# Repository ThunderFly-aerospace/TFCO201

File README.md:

# TFCO201 - ThunderFly airborne CO2 concentration sensor

The TFCO201 [carbon dioxide gas](https://en.wikipedia.org/wiki/Carbon_dioxide) sensor offers flexible integration options. It can be directly connected to a Pixhawk autopilot with PX4 firmware or used as a sensor for the [TF-ATMON monitoring system](https://www.thunderfly.cz/tf-atmon.html).

Sensors mounted on UAVs can be used for a variety of purposes. TFCO201 can measure CO2 concentrations in parallel with air temperature and humidity, which can be used for meteorological purposes. It could also be used to determine the presence of wildfires.

## Applications

In combination with the [TF-ATMON system](https://www.thunderfly.cz/tf-atmon.html), the sensor could be used in various applications. Here are a few examples. 

### Atmospheric sounding

The TFCO201 sensor could be used for [direct atmospheric sounding](https://en.wikipedia.org/wiki/Atmospheric_sounding). Here is an example of measured data taken by [TF-G2 autogyro](https://www.thunderfly.cz/tf-g2.html).

### Locating sources of atmospheric pollution (Urban Air Quality Monitoring)

A drone with a CO2 sensor can monitor carbon dioxide levels in densely populated urban areas, such UAVs can collect data on CO2 concentrations across different parts of the city, aiding authorities in identifying and addressing areas with high emissions. This data can be utilized for green space planning, improving urban transportation, and informing residents about air quality.

### Ecosystem Change Observation 
An unmanned system with a CO2 sensor can monitor changes in CO2 levels in various ecosystems, such as forests, wetlands, or agricultural lands. This information is crucial for scientists studying the impact of climate change on different types of environments and aids in predicting future ecological changes or impact mitigation methods. 

### Industrial Emission Control 
Industrial areas often contribute significantly to total CO2 emissions. A UAV with a CO2 sensor can effectively monitor and map emissions from factories, power plants, and other industrial facilities. This data can be used for emission regulation and developing strategies to reduce the carbon footprint of industrial areas.

## Where to get it?

The TFCO201 is commercially available from [ThunderFly s.r.o.](https://www.thunderfly.cz/). For a commercial quotation, contact us by email at sale@thunderfly.cz or shop at our [Tindie store](https://www.tindie.com/stores/thunderfly/).

## Parameters

| Parameter | Value | Description |
|-----------|-------|-------------|
| Sensing element | [SCD41](https://sensirion.com/media/documents/E0F04247/631EF271/CD_DS_SCD40_SCD41_Datasheet_D1.pdf) | Other possible sensors SCD40, SCD42 |
| Typical accuracy | ± (50 ppm + 5% of reading) | 400 ppm – 2’000 ppm  |
| Humidity measurement accuracy | ± 9 % RH | -10 °C – 60 °C, 0 %RH – 100 %RH  |
| Temperature measurement accuracy | ± 1.5 °C | -10 °C – 60 °C |
| Repeatability | ± 10 ppm |  |
| Operating temperature range| -10 °C – 60 °C |  |
| Operating humidity range| 0 %RH – 100 %RH | |
| I2C connector | 4-pin JST-GH | The second connector could be installed on the opposite side |
| I2C address | 0x62 | can be changed by using the [TFI2CADT01](https://github.com/ThunderFly-aerospace/TFI2CADT01) |
| Storage temperature range| -20 °C - +40 °C |  |
| Operational input voltage | 3.6 - 5.4V | Overvoltage internally protected by zener diode |
| Mass | 3 g | PCB, without cabling |
| Dimensions | 30 x 15 x 6.5 mm |  PCB |
| Weather resistance | IP40 | External connectors fully occupied.  |

## Schematics

## Usage in PX4
~~The sensor is currently supported by the PX4 autopilot. Multiple sensors can be connected to one autopilot. The measured data are immediately sent to the ground station and they are also logged in the onboard ulog file.~~

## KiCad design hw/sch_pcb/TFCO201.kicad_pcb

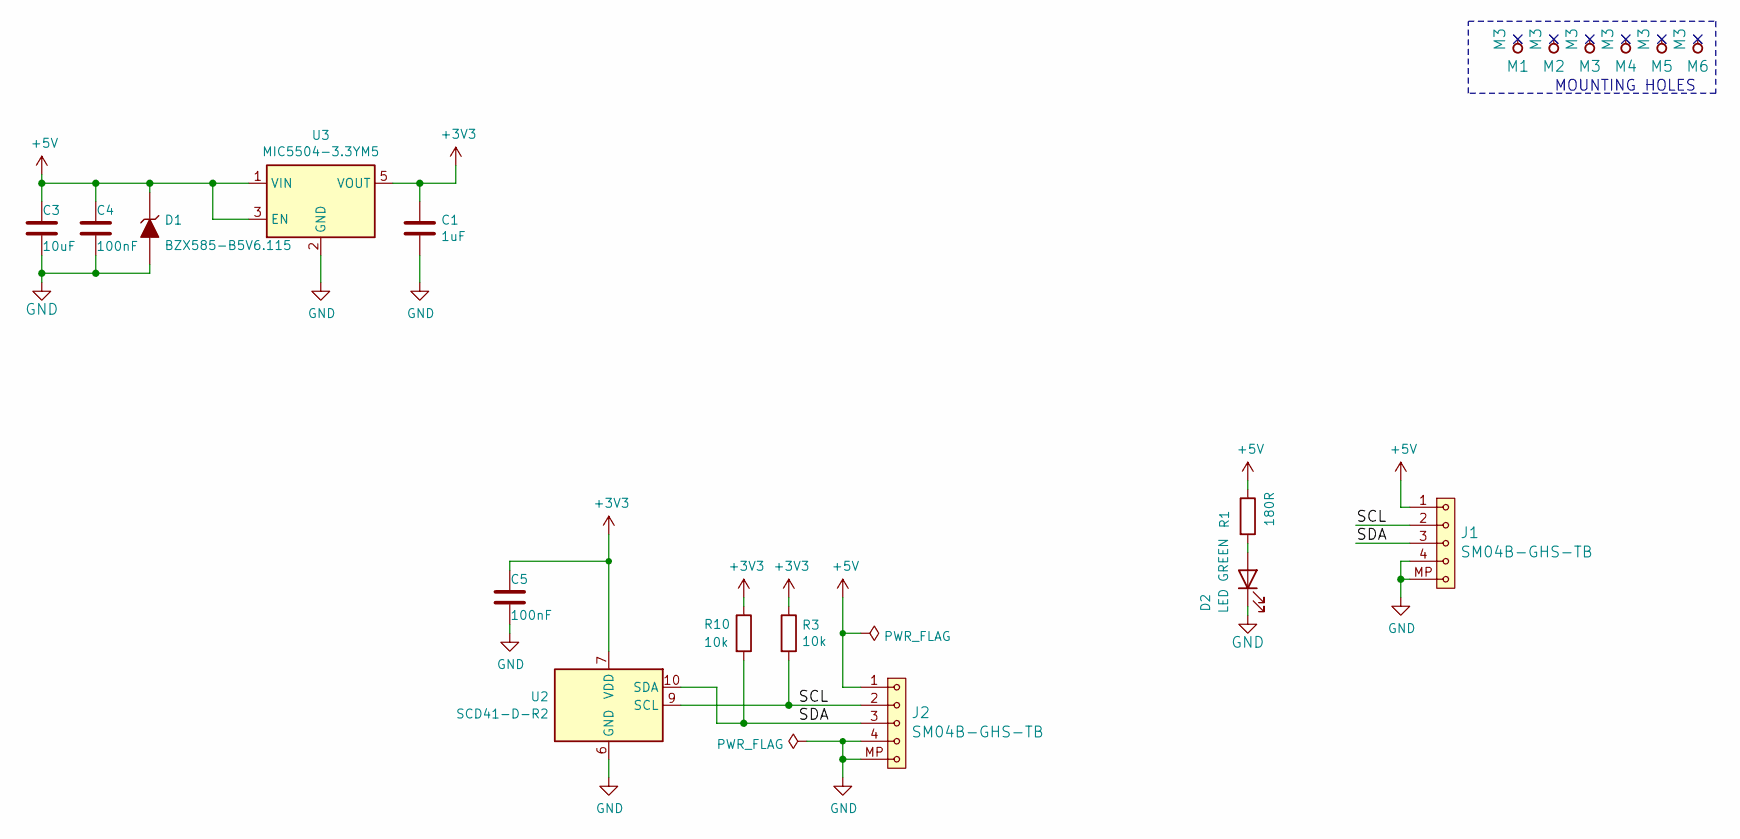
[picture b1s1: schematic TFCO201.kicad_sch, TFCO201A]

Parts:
C1: 1uF; SMD-0603
C3: 10uF; SMD-0805
C4, C5: 100nF; SMD-0603
D1: BZX585-B5V6.115; D_SOD-523
D2: LED GREEN; LED_1206_mill
J1, J2: SM04B-GHS-TB; JST_GH_SM04B-GHS-TB_1x04-1MP_P1.25mm_Horizontal
M1, M2, M3, M4, M5, M6: M3; dira_3mm
R1: 180R; SMD-0603
R3, R10: 10k; SMD-0603
U2: SCD41-D-R2; Sensirion_SCD4x-1EP_10.1x10.1mm_P1.25mm_EP4.8x4.8mm
U3: MIC5504-3.3YM5; SOT-23-5

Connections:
+3V3: C1.1, C5.1, R3.1, R10.1, U2.7 (VDD), U2.19 (VDD), U3.5 (VOUT)
+5V: C3.1, C4.1, D1.1 (K), J1.1, J2.1, R1.1, U3.1 (VIN), U3.3 (EN)
/SCL: J1.2, J2.2, R3.2, U2.9 (SCL)
/SDA: J1.3, J2.3, R10.2, U2.10 (SDA)
GND: C1.2, C3.2, C4.2, C5.2, D1.2 (A), D2.1 (K), J1.4, J1.MP, J2.4, J2.MP, U2.6 (GND), U2.20 (GND), U2.21 (GND), U3.2 (GND)
unnamed: D2.2 (A), R1.2

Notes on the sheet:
MOUNTING HOLES

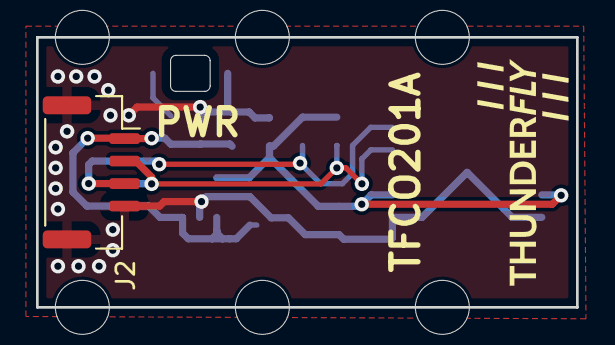
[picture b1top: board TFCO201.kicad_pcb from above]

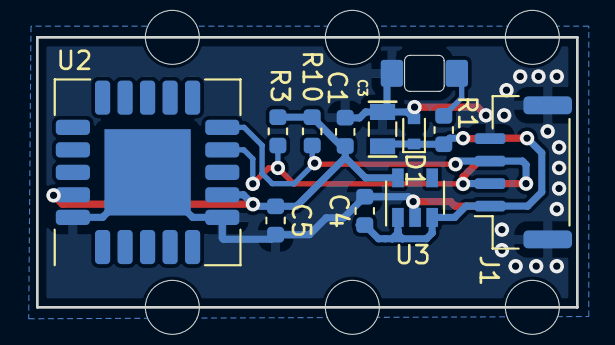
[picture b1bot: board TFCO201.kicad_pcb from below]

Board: 2 copper layers, 30.0 x 15.0 mm, 19 parts (12 on the bottom side), 6 nets.

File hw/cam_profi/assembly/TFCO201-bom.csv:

Component,Description,Part,References,Value,Footprint,Quantity Per PCB,Datasheet,ust_id
1,Unpolarized capacitor,C,C4C5,100nF,SMD-0603,2,~,5c70984812875079b91f8bf2
2,Unpolarized capacitor,C,C1,1uF,SMD-0603,1,~,5c70984812875079b91f8bc2
3,Unpolarized capacitor,C,C3,10uF,SMD-0805,1,~,5c70984812875079b91f8bbd
4,,D_ZENER,D1,BZX585-B5V6.115,D_SOD-523,1,,60879d38128750769ee58e48
5,Light emitting diode,LED,D2,LED GREEN,LED_1206_mill,1,~,5c70984412875079b91f8895
6,,SM04B-GHS-TB,J1J2,SM04B-GHS-TB,JST_GH_SM04B-GHS-TB_1x04-1MP_P1.25mm_Horizontal,2,,5c86273d1287500b4e0280be
7,,HOLE,M1M2M3M4M5M6,M3,dira_3mm,6,,
8,Resistor,R,R1,180R,SMD-0603,1,~,5c70984512875079b91f8957
9,Resistor,R,R3R10,10k,SMD-0603,2,~,5c70984512875079b91f8962
10,"300mA Low-dropout Voltage Regulator, Vout 3.3V, Vin up to 5.5V, SOT-23",MIC5504-3.3YM5,U3,MIC5504-3.3YM5,SOT-23-5,1,http://ww1.microchip.com/downloads/en/DeviceDoc/MIC550X.pdf,5c7255e81287500b4e112ea2
11,"Photoacoustic CO2 sensor, 40 000 ppm, I2C, 2.4-5.5 V, High accuracy  400 - 5000 ppm",SCD41-D-R2,U2,SCD41-D-R2,Sensirion_SCD4x-1EP_10.1x10.1mm_P1.25mm_EP4.8x4.8mm,1,https://sensirion.com/media/documents/E0F04247/631EF271/CD_D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,

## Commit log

2023-10-01 Initial version of ThunderFly CO2 sensor.
2023-10-01 Update README.md
    Modify the readme to the current sensor version.
2023-10-01 Update actions products
2023-10-01 Update README.md
    Fix the link to images.
2023-10-01 Update title block.
2023-10-01 Update README.md
    Fix link.
2023-11-13 Update workflow files
2025-01-10 Cleanup unrelated files.
2025-01-11 Update project.
